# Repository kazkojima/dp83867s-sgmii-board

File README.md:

# KiCAD files of a SGMII PHY board with TI DP83867S

KiCAD files of a simple SGMII PHY

It works with an ECP5 evaluation board LFE5UM5G-85F-EVN running [LiteX](https://github.com/enjoy-digital/litex).

## Problems

* 1.0V LDO will be too hot when supplying 5V. It should be bigger package which has lower junction thermal resistance. 3.3V supply will be OK.

* SMA connectors were a bit too close to each other.

* REFCLK LDVS and CLKOUT outputs could be optional because almost MACs has their own CDR.

* Datasheet says "at minimum a 4-layer PCB should be used. However a 6-layer board is recommended." This 2-layer PCB violates it :-)

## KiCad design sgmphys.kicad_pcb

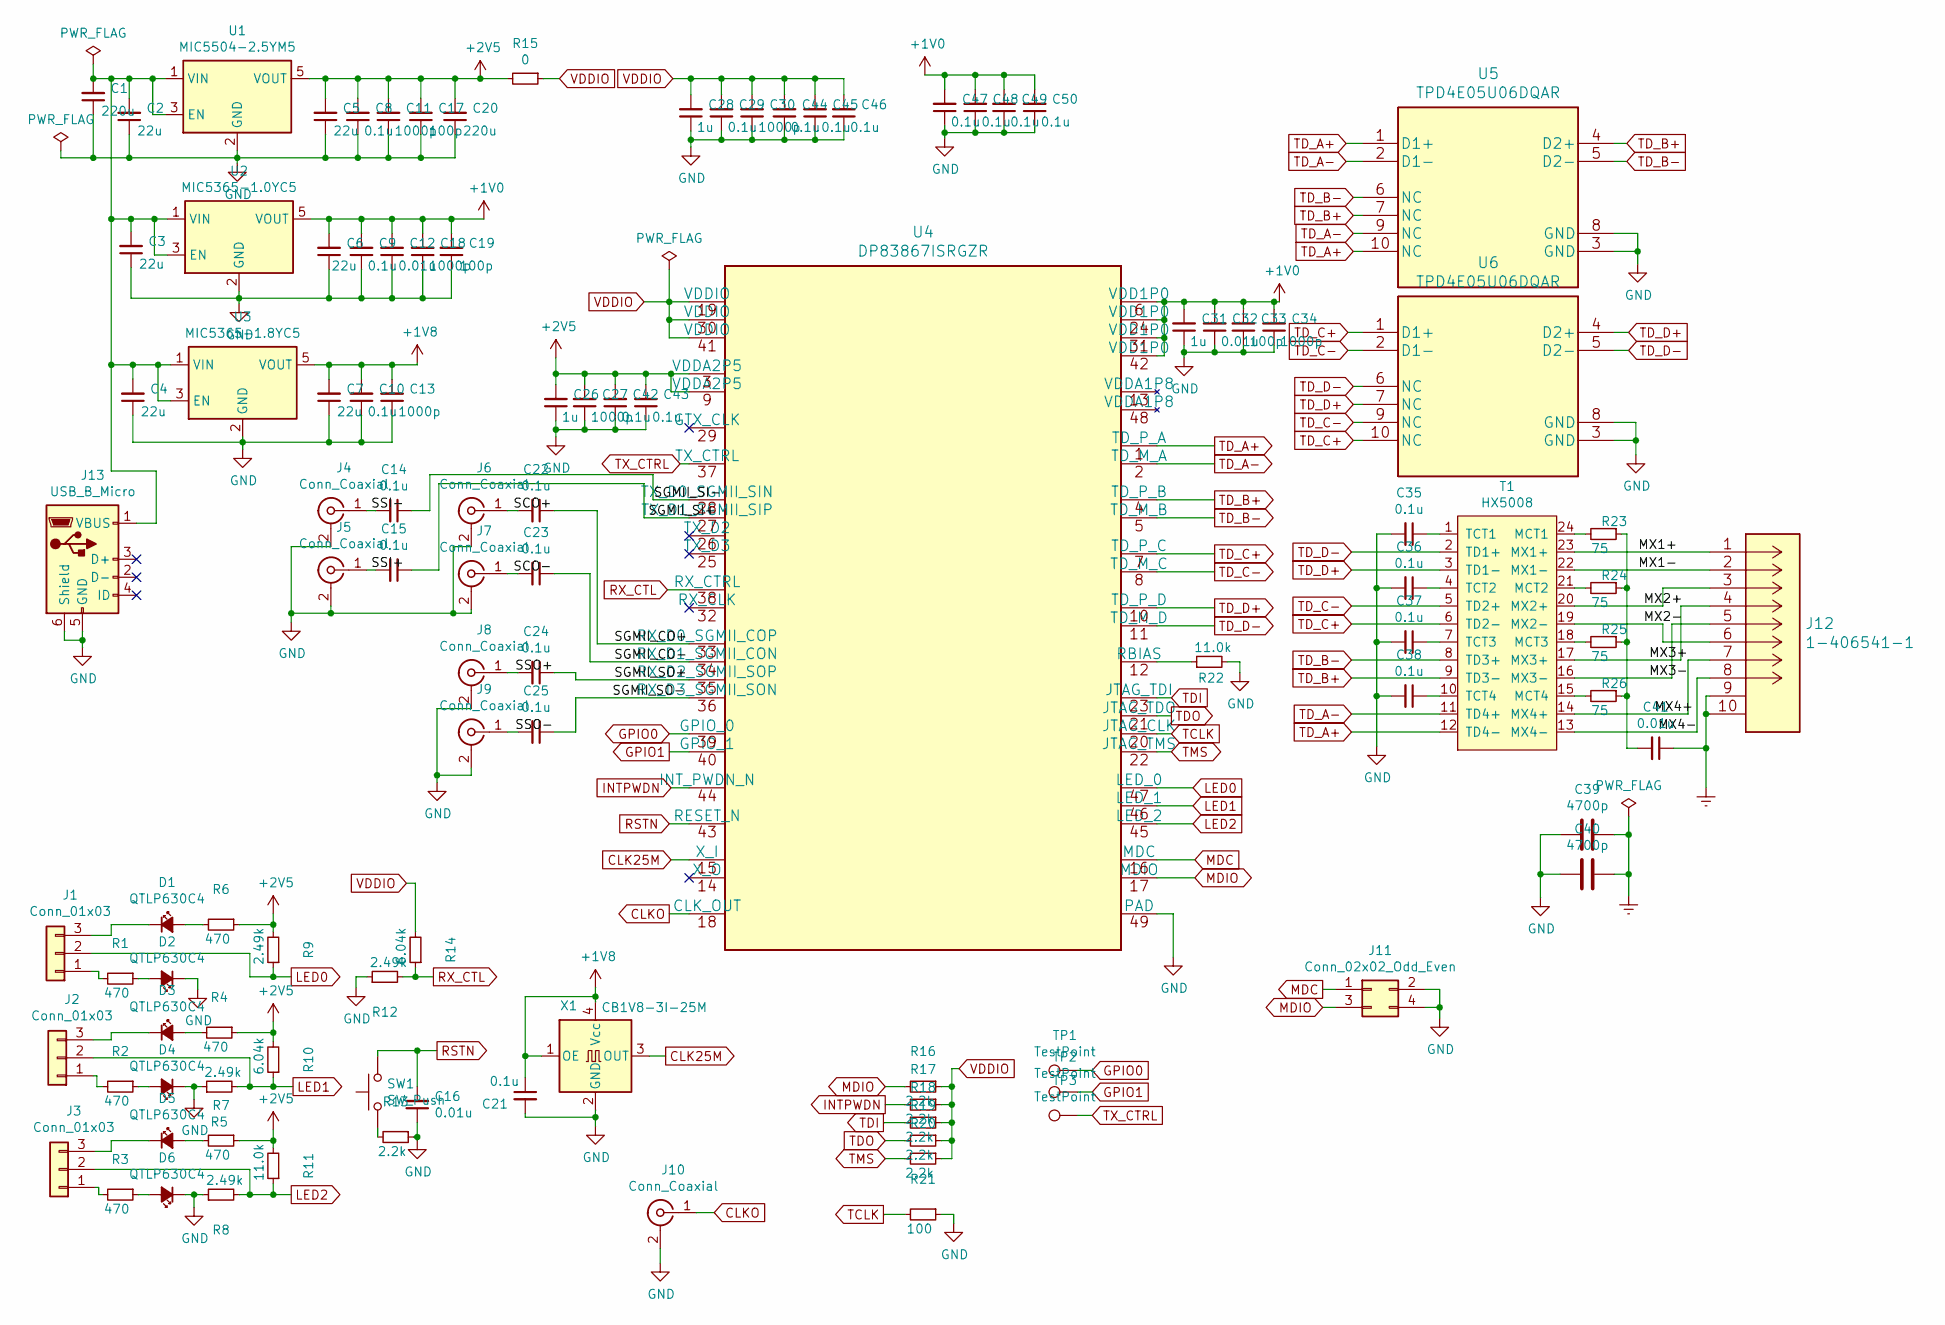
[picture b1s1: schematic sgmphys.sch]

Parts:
C1, C20: 220u; C_1210_3225Metric
C2, C3, C4, C5, C6, C7: 22u; C_0603_1608Metric
C8, C9, C10, C14, C15, C21, C22, C23, C24, C25, C29, C35, C36, C37, C38, C42, C43, C44, C45, C46, C47, C48, C49, C50: 0.1u; C_0402_1005Metric
C11, C13, C18, C27, C30, C34: 1000p; C_0402_1005Metric
C12, C16, C32, C41: 0.01u; C_0402_1005Metric
C17, C19, C33: 100p; C_0402_1005Metric
C26, C28, C31: 1u; C_0402_1005Metric
C39, C40: 4700p; C_1812_4532Metric
D1, D2, D3, D4, D5, D6: QTLP630C4; D_0805_2012Metric
J1, J2, J3: Conn_01x03; PinHeader_1x03_P2.54mm_Vertical
J4, J5, J6, J7, J8, J9, J10: Conn_Coaxial; SMA_Amphenol_132134_Vertical
J11: Conn_02x02_Odd_Even; PinHeader_2x02_P2.54mm_Vertical
J12: 1-406541-1
J13: USB_B_Micro; USB_Micro-B_Molex-105017-0001
R1, R2, R3, R4, R6, R7: 470; R_0402_1005Metric
R5, R8, R9, R12: 2.49k; R_0402_1005Metric
R10, R14: 6.04k; R_0402_1005Metric
R11, R22: 11.0k; R_0402_1005Metric
R13, R16, R17, R18, R19, R20: 2.2k; R_0402_1005Metric
R15: 0; R_0603_1608Metric
R21: 100; R_0402_1005Metric
R23, R24, R25, R26: 75; R_0402_1005Metric
SW1: SW_Push; SW_SPST_B3U-1000P
T1: HX5008; HX5008NL
TP1, TP2, TP3: TestPoint; TestPoint_Pad_D1.0mm
U1: MIC5504-2.5YM5; SOT-23-5
U2: MIC5365-1.0YC5; SOT-353_SC-70-5
U3: MIC5365-1.8YC5; SOT-353_SC-70-5
U4: DP83867ISRGZR
U5, U6: TPD4E05U06DQAR
X1: CB1V8-3I-25M; Oscillator_SMD_SeikoEpson_SG8002CA-4Pin_7.0x5.0mm

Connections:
+1V0: C6.2, C9.2, C12.2, C18.2, C19.2, C31.2, C32.2, C33.2, C34.2, C47.2, C48.2, C49.2, C50.2, U2.5 (VOUT), U4.6 (VDD1P0), U4.24 (VDD1P0), U4.31 (VDD1P0), U4.42 (VDD1P0)
+1V8: C7.2, C10.2, C13.2, C21.1, U3.5 (VOUT), X1.1 (OE), X1.4 (Vcc)
+2V5: C5.2, C8.2, C11.2, C17.2, C20.2, C26.2, C27.2, C42.2, C43.2, R4.1, R6.1, R7.1, R9.2, R10.2, R11.2, R15.2, U1.5 (VOUT), U4.3 (VDDA2P5), U4.9 (VDDA2P5)
/MX1+: J12.1, T1.23 (MX1+)
/MX1-: J12.2, T1.22 (MX1-)
/MX2+: J12.3, T1.20 (MX2+)
/MX2-: J12.6, T1.19 (MX2-)
/MX3+: J12.4, T1.17 (MX3+)
/MX3-: J12.5, T1.16 (MX3-)
/MX4+: J12.7, T1.14 (MX4+)
/MX4-: J12.8, T1.13 (MX4-)
/SCO+: C22.2, J6.1 (In)
/SCO-: C23.2, J7.1 (In)
/SGMII_CO+: C22.1, U4.33 (RX_D0_SGMII_COP)
/SGMII_CO-: C23.1, U4.34 (RX_D1_SGMII_CON)
/SGMII_SI+: C15.1, U4.27 (TX_D1_SGMII_SIP)
/SGMII_SI-: C14.1, U4.28 (TX_D0_SGMII_SIN)
/SGMII_SO+: C24.1, U4.35 (RX_D2_SGMII_SOP)
/SGMII_SO-: C25.1, U4.36 (RX_D3_SGMII_SON)
/SSI+: C15.2, J5.1 (In)
/SSI-: C14.2, J4.1 (In)
/SSO+: C24.2, J8.1 (In)
/SSO-: C25.2, J9.1 (In)
CLK25M: U4.15 (X_I), X1.3 (OUT)
CLKO: J10.1 (In), U4.18 (CLK_OUT)
Earth: C39.1, C40.1, C41.1, J12.9 (SHIELD), J12.10 (SHIELD)
GND: C1.1, C2.1, C3.1, C4.1, C5.1, C6.1, C7.1, C8.1, C9.1, C10.1, C11.1, C12.1, C13.1, C16.1, C17.1, C18.1, C19.1, C20.1, C21.2, C26.1, C27.1, C28.1, C29.1, C30.1, C31.1, C32.1, C33.1, C34.1, C35.2, C36.2, C37.2, C38.2, C39.2, C40.2, C42.1, C43.1, C44.1, C45.1, C46.1, C47.1, C48.1, C49.1, C50.1, D2.1 (K), D4.1 (K), D6.1 (K), J4.2 (Ext), J5.2 (Ext), J6.2 (Ext), J7.2 (Ext), J8.2 (Ext), J9.2 (Ext), J10.2 (Ext), J11.2, J11.4, J13.5 (GND), J13.6 (Shield), R5.1, R8.1, R12.1, R13.1, R21.1, R22.2, U1.2 (GND), U2.2 (GND), U3.2 (GND), U4.49 (PAD), U4.V, U5.3 (GND), U5.8 (GND), U6.3 (GND), U6.8 (GND), X1.2 (GND)
GPIO0: TP1.1, U4.39 (GPIO_0)
GPIO1: TP2.1, U4.40 (GPIO_1)
INTPWDN: R17.2, U4.44 (INT_PWDN_N)
LED0: J1.2, R9.1, U4.47 (LED_0)
LED1: J2.2, R5.2, R10.1, U4.46 (LED_1)
LED2: J3.2, R8.2, R11.1, U4.45 (LED_2)
MDC: J11.1, U4.16 (MDC)
MDIO: J11.3, R16.2, U4.17 (MDIO)
unnamed: C1.2, C2.2, C3.2, C4.2, J13.1 (VBUS), U1.1 (VIN), U1.3 (EN), U2.1 (VIN), U2.3 (EN), U3.1 (VIN), U3.3 (EN)
unnamed: C35.1, T1.1 (TCT1)
unnamed: C36.1, T1.4 (TCT2)
unnamed: C37.1, T1.7 (TCT3)
unnamed: C38.1, T1.10 (TCT4)
unnamed: C41.2, R23.1, R24.1, R25.1, R26.1
unnamed: D1.1 (K), J1.3
unnamed: D1.2 (A), R6.2
unnamed: D2.2 (A), R1.1
unnamed: D3.1 (K), J2.3
unnamed: D3.2 (A), R4.2
unnamed: D4.2 (A), R2.1
unnamed: D5.1 (K), J3.3
unnamed: D5.2 (A), R7.2
unnamed: D6.2 (A), R3.1
unnamed: J1.1, R1.2
unnamed: J2.1, R2.2
unnamed: J3.1, R3.2
unnamed: R13.2, SW1.1
unnamed: R22.1, U4.12 (RBIAS)
unnamed: R23.2, T1.24 (MCT1)
unnamed: R24.2, T1.21 (MCT2)
unnamed: R25.2, T1.18 (MCT3)
unnamed: R26.2, T1.15 (MCT4)
RSTN: C16.2, SW1.2, U4.43 (RESET_N)
RX_CTL: R12.2, R14.1, U4.38 (RX_CTRL)
TCLK: R21.2, U4.20 (JTAG_CLK)
TDI: R18.2, U4.23 (JTAG_TDI)
TDO: R19.2, U4.21 (JTAG_TDO)
TD_A+: T1.12 (TD4-), U4.1 (TD_P_A), U5.1 (D1+), U5.10 (NC)
TD_A-: T1.11 (TD4+), U4.2 (TD_M_A), U5.2 (D1-), U5.9 (NC)
TD_B+: T1.9 (TD3-), U4.4 (TD_P_B), U5.4 (D2+), U5.7 (NC)
TD_B-: T1.8 (TD3+), U4.5 (TD_M_B), U5.5 (D2-), U5.6 (NC)
TD_C+: T1.6 (TD2-), U4.7 (TD_P_C), U6.1 (D1+), U6.10 (NC)
TD_C-: T1.5 (TD2+), U4.8 (TD_M_C), U6.2 (D1-), U6.9 (NC)
TD_D+: T1.3 (TD1-), U4.10 (TD_P_D), U6.4 (D2+), U6.7 (NC)
TD_D-: T1.2 (TD1+), U4.11 (TD_M_D), U6.5 (D2-), U6.6 (NC)
TMS: R20.2, U4.22 (JTAG_TMS)
TX_CTRL: TP3.1, U4.37 (TX_CTRL)
VDDIO: C28.2, C29.2, C30.2, C44.2, C45.2, C46.2, R14.2, R15.1, R16.1, R17.1, R18.1, R19.1, R20.1, U4.19 (VDDIO), U4.30 (VDDIO), U4.41 (VDDIO)

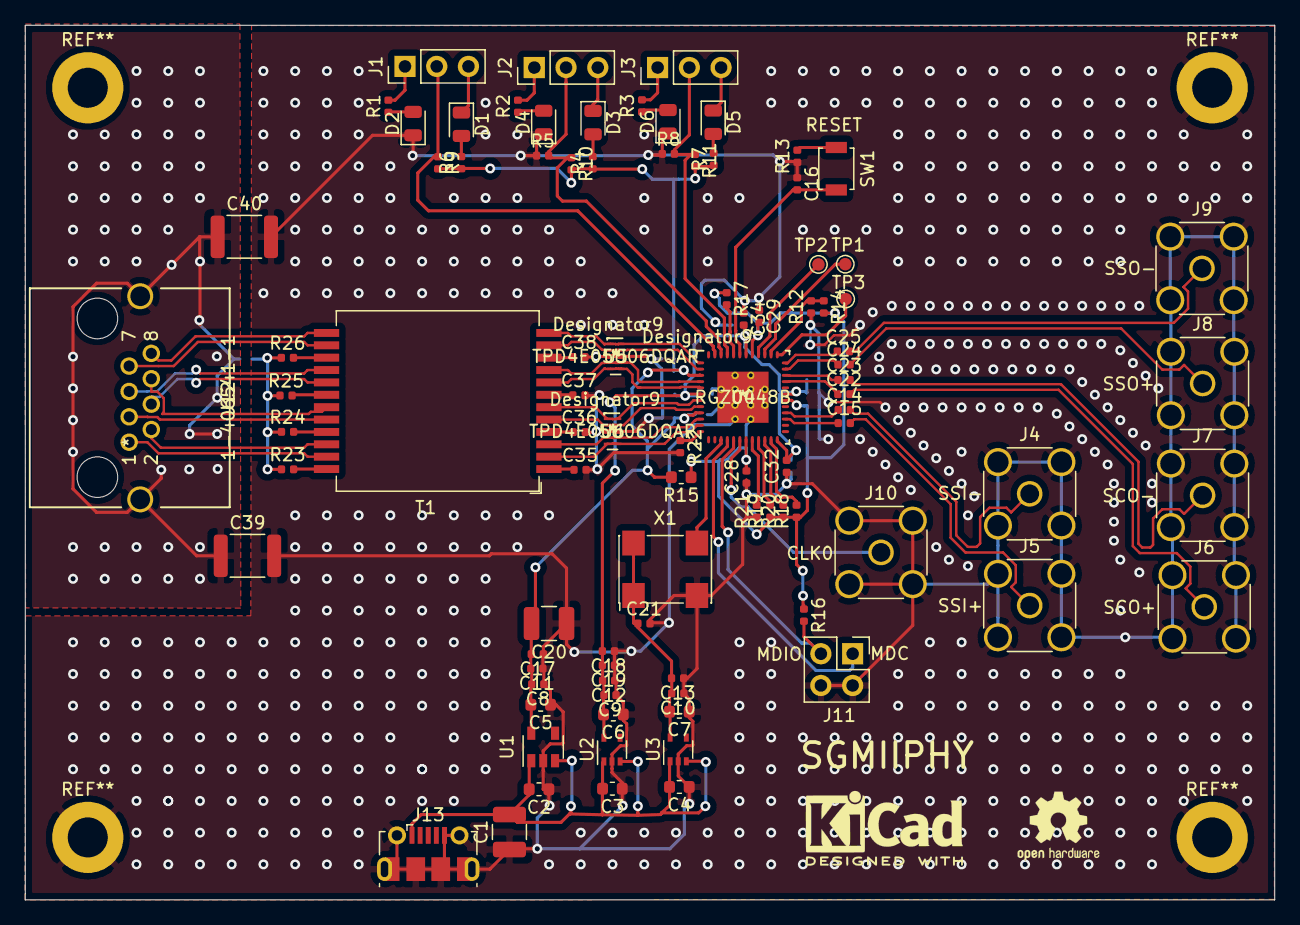
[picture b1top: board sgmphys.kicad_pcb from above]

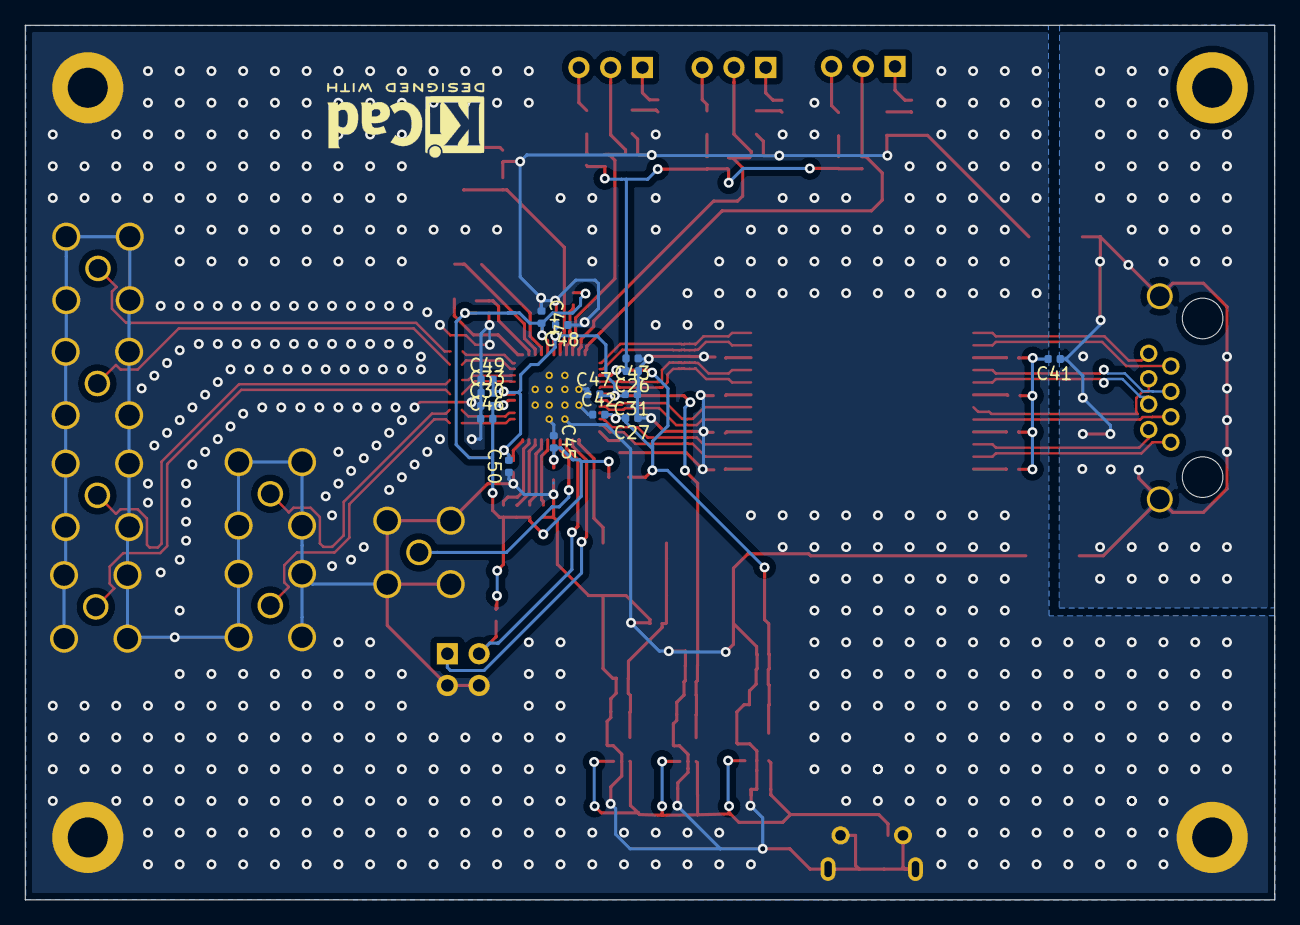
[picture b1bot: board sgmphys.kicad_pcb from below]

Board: 2 copper layers, 100.0 x 70.0 mm, 107 parts (15 on the bottom side), 75 nets.

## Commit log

2021-05-16 Initial commit.
2021-05-16 Add images.
2021-05-16 Fix .gitignore.

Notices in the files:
parts and their libraries:
Copyright 2016 Accelerated Designs. All rights reserved.
